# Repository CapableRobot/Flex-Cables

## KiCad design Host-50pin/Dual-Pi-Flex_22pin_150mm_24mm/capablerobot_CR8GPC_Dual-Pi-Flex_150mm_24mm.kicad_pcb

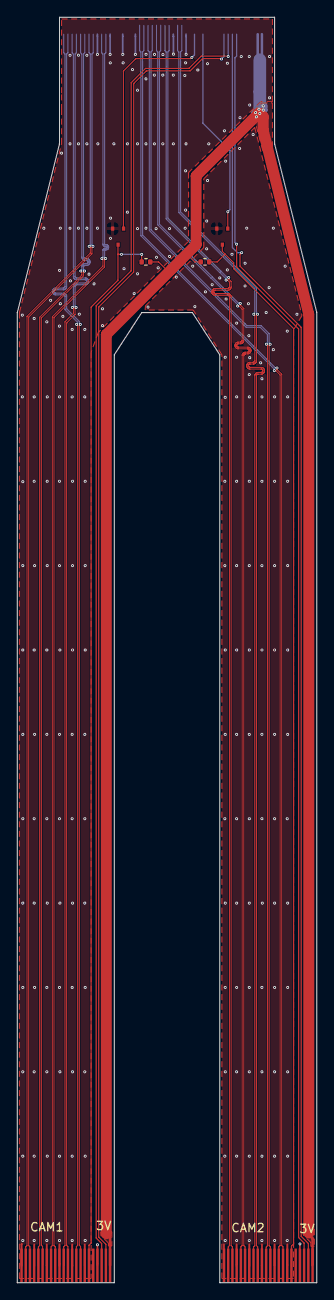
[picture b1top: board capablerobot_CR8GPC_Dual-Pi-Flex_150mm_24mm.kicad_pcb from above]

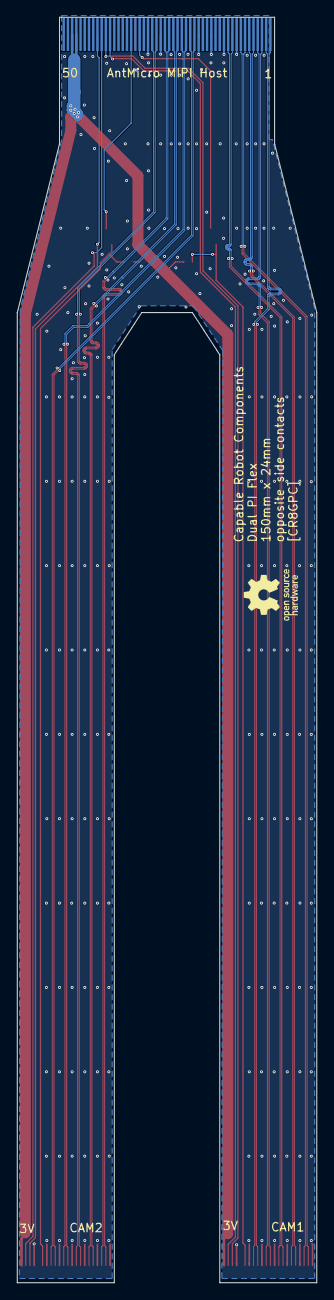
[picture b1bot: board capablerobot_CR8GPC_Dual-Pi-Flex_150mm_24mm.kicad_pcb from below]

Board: 2 copper layers, 35.5 x 150.0 mm, 8 parts (2 on the bottom side), 30 nets.

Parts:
AntMicro MIPI Host: WE_687650100002_FLEX
CAM1, CAM2: WE_687622100002_FLEX
N1: oshw_logo; oshw-logo
Q1, Q2: BSS138APW; SC70-3
R1, R2: R; R_0402_1005Metric

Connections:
/F1_3.3V: AntMicro MIPI Host.47, AntMicro MIPI Host.48, CAM1.22, CAM2.22, R1.2, R2.2
/F1_C1_CSI0_CLK_N: AntMicro MIPI Host.10, CAM1.8
/F1_C1_CSI0_CLK_P: AntMicro MIPI Host.11, CAM1.9
/F1_C1_CSI0_D0_N: AntMicro MIPI Host.7, CAM1.2
/F1_C1_CSI0_D0_P: AntMicro MIPI Host.8, CAM1.3
/F1_C1_CSI0_D1_N: AntMicro MIPI Host.5, CAM1.5
/F1_C1_CSI0_D1_P: AntMicro MIPI Host.6, CAM1.6
/F1_C1_CSI1_D0_N: AntMicro MIPI Host.3, CAM1.11
/F1_C1_CSI1_D0_P: AntMicro MIPI Host.4, CAM1.12
/F1_C1_CSI1_D1_N: AntMicro MIPI Host.1, CAM1.14
/F1_C1_CSI1_D1_P: AntMicro MIPI Host.2, CAM1.15
/F1_C1_SCL: AntMicro MIPI Host.40, CAM1.20
/F1_C1_SDA: AntMicro MIPI Host.39, CAM1.21
/F1_C1_VSYNC: AntMicro MIPI Host.32, Q1.1
/F1_C1_VSYNCHV: CAM1.17, Q1.3, R1.1
/F1_C2_CSI0_CLK_N: AntMicro MIPI Host.28, CAM2.8
/F1_C2_CSI0_CLK_P: AntMicro MIPI Host.29, CAM2.9
/F1_C2_CSI0_D0_N: AntMicro MIPI Host.25, CAM2.2
/F1_C2_CSI0_D0_P: AntMicro MIPI Host.26, CAM2.3
/F1_C2_CSI0_D1_N: AntMicro MIPI Host.23, CAM2.5
/F1_C2_CSI0_D1_P: AntMicro MIPI Host.24, CAM2.6
/F1_C2_CSI1_D0_N: AntMicro MIPI Host.21, CAM2.11
/F1_C2_CSI1_D0_P: AntMicro MIPI Host.22, CAM2.12
/F1_C2_CSI1_D1_N: AntMicro MIPI Host.19, CAM2.14
/F1_C2_CSI1_D1_P: AntMicro MIPI Host.20, CAM2.15
/F1_C2_SCL: AntMicro MIPI Host.42, CAM2.20
/F1_C2_SDA: AntMicro MIPI Host.41, CAM2.21
/F1_C2_VSYNC: AntMicro MIPI Host.34, Q2.1
/F1_C2_VSYNCHV: CAM2.17, Q2.3, R2.1
/F1_GND: AntMicro MIPI Host.9, AntMicro MIPI Host.12, AntMicro MIPI Host.15, AntMicro MIPI Host.18, AntMicro MIPI Host.27, AntMicro MIPI Host.30, CAM1.1, CAM1.4, CAM1.7, CAM1.10, CAM1.13, CAM1.16, CAM1.19, CAM2.1, CAM2.4, CAM2.7, CAM2.10, CAM2.13, CAM2.16, CAM2.19, Q1.2, Q2.2

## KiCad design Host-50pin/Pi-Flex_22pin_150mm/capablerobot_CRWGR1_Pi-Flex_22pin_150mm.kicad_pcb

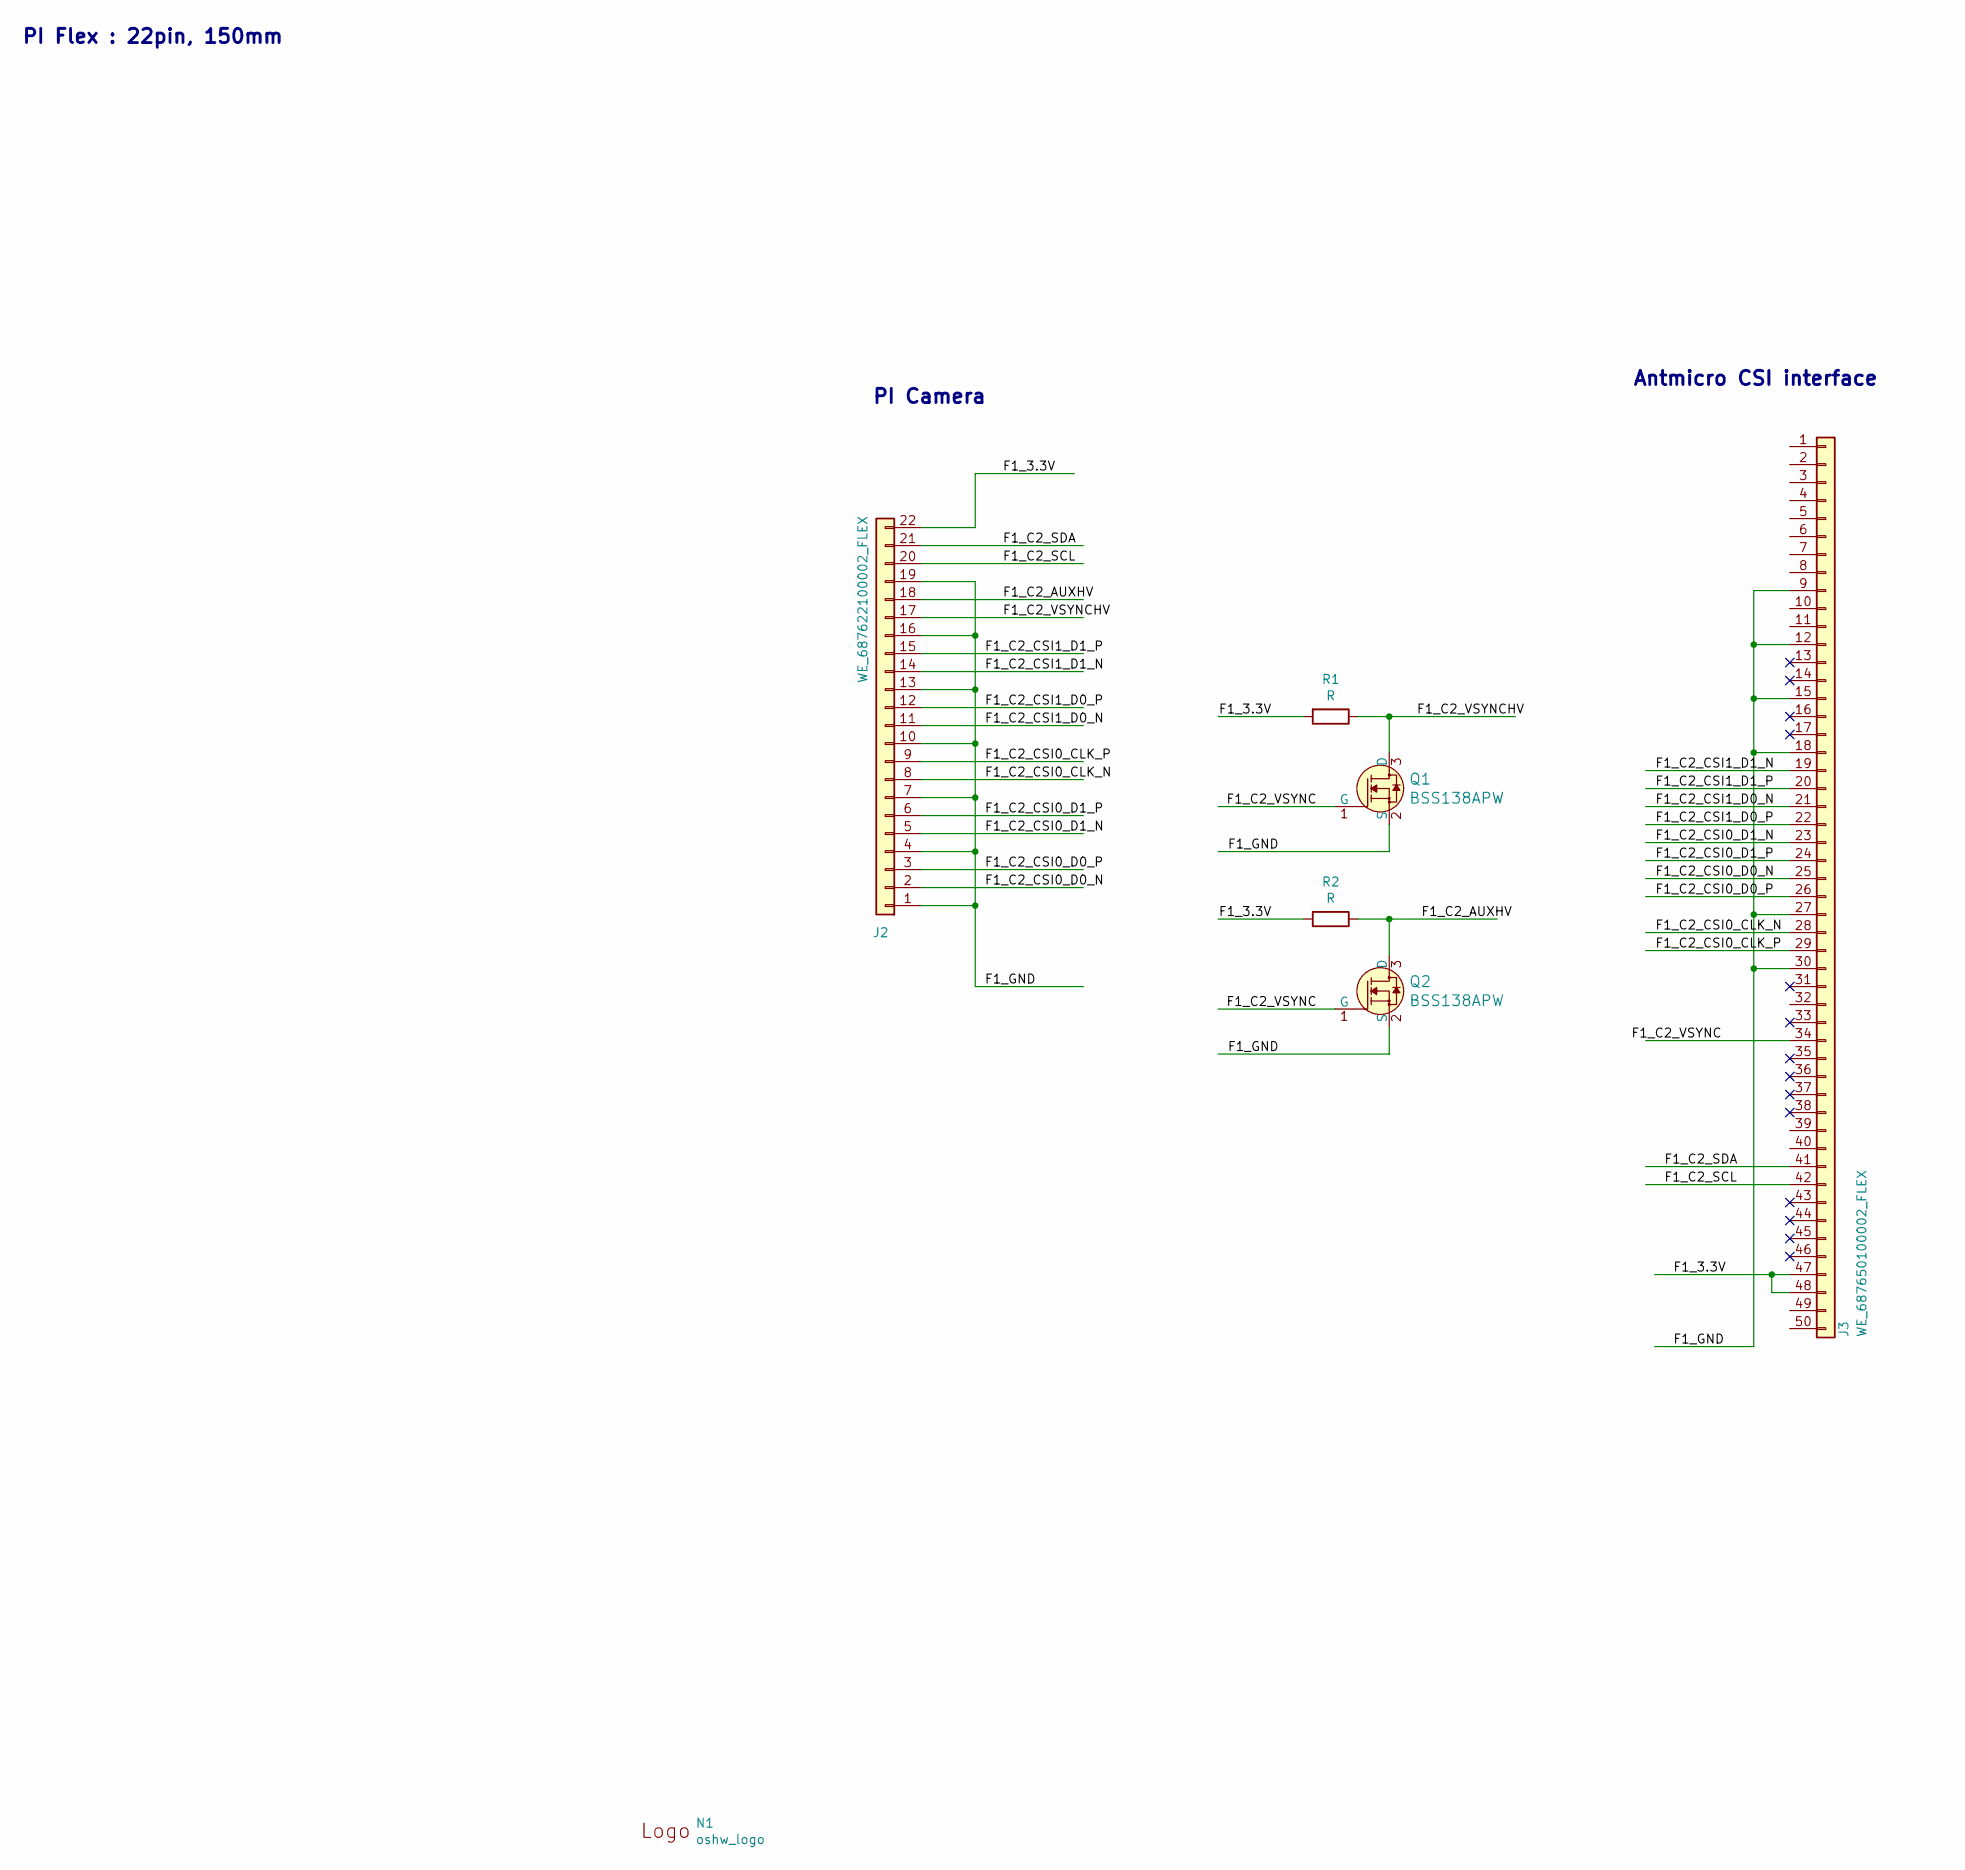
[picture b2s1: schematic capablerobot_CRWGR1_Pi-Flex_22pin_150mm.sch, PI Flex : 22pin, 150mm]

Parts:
J2: WE_687622100002_FLEX; MPN 687622100002
J3: WE_687650100002_FLEX; MPN 687650100002
N1: oshw_logo; oshw-logo
Q1, Q2: BSS138APW; SC70-3; MPN BSS138PW
R1, R2: R; R_0402_1005Metric

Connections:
/F1_3.3V: J2.22, J3.47, J3.48, R1.2, R2.2
/F1_C2_AUXHV: J2.18, Q2.3 (D), R2.1
/F1_C2_CSI0_CLK_N: J2.8, J3.28
/F1_C2_CSI0_CLK_P: J2.9, J3.29
/F1_C2_CSI0_D0_N: J2.2, J3.25
/F1_C2_CSI0_D0_P: J2.3, J3.26
/F1_C2_CSI0_D1_N: J2.5, J3.23
/F1_C2_CSI0_D1_P: J2.6, J3.24
/F1_C2_CSI1_D0_N: J2.11, J3.21
/F1_C2_CSI1_D0_P: J2.12, J3.22
/F1_C2_CSI1_D1_N: J2.14, J3.19
/F1_C2_CSI1_D1_P: J2.15, J3.20
/F1_C2_SCL: J2.20, J3.42
/F1_C2_SDA: J2.21, J3.41
/F1_C2_VSYNC: J3.34, Q1.1 (G), Q2.1 (G)
/F1_C2_VSYNCHV: J2.17, Q1.3 (D), R1.1
/F1_GND: J2.1, J2.4, J2.7, J2.10, J2.13, J2.16, J2.19, J3.9, J3.12, J3.15, J3.18, J3.27, J3.30, Q1.2 (S), Q2.2 (S)

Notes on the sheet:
PI Camera
Antmicro CSI interface
PI Flex : 22pin, 150mm

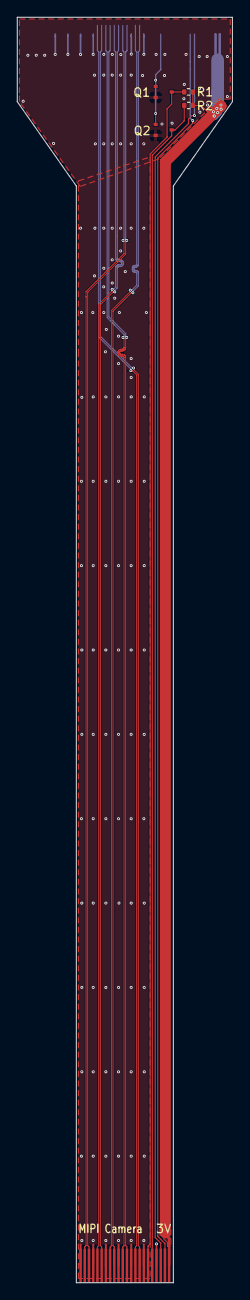
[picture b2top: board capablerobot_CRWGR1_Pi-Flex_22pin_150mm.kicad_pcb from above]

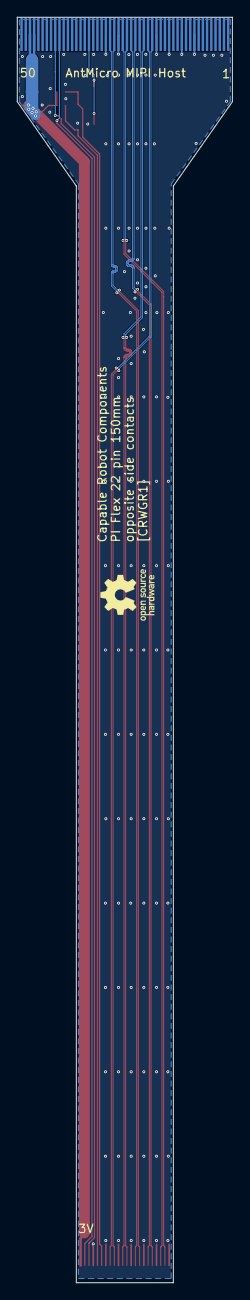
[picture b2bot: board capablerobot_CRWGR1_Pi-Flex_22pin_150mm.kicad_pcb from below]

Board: 2 copper layers, 25.5 x 150.0 mm, 7 parts (2 on the bottom side), 17 nets.

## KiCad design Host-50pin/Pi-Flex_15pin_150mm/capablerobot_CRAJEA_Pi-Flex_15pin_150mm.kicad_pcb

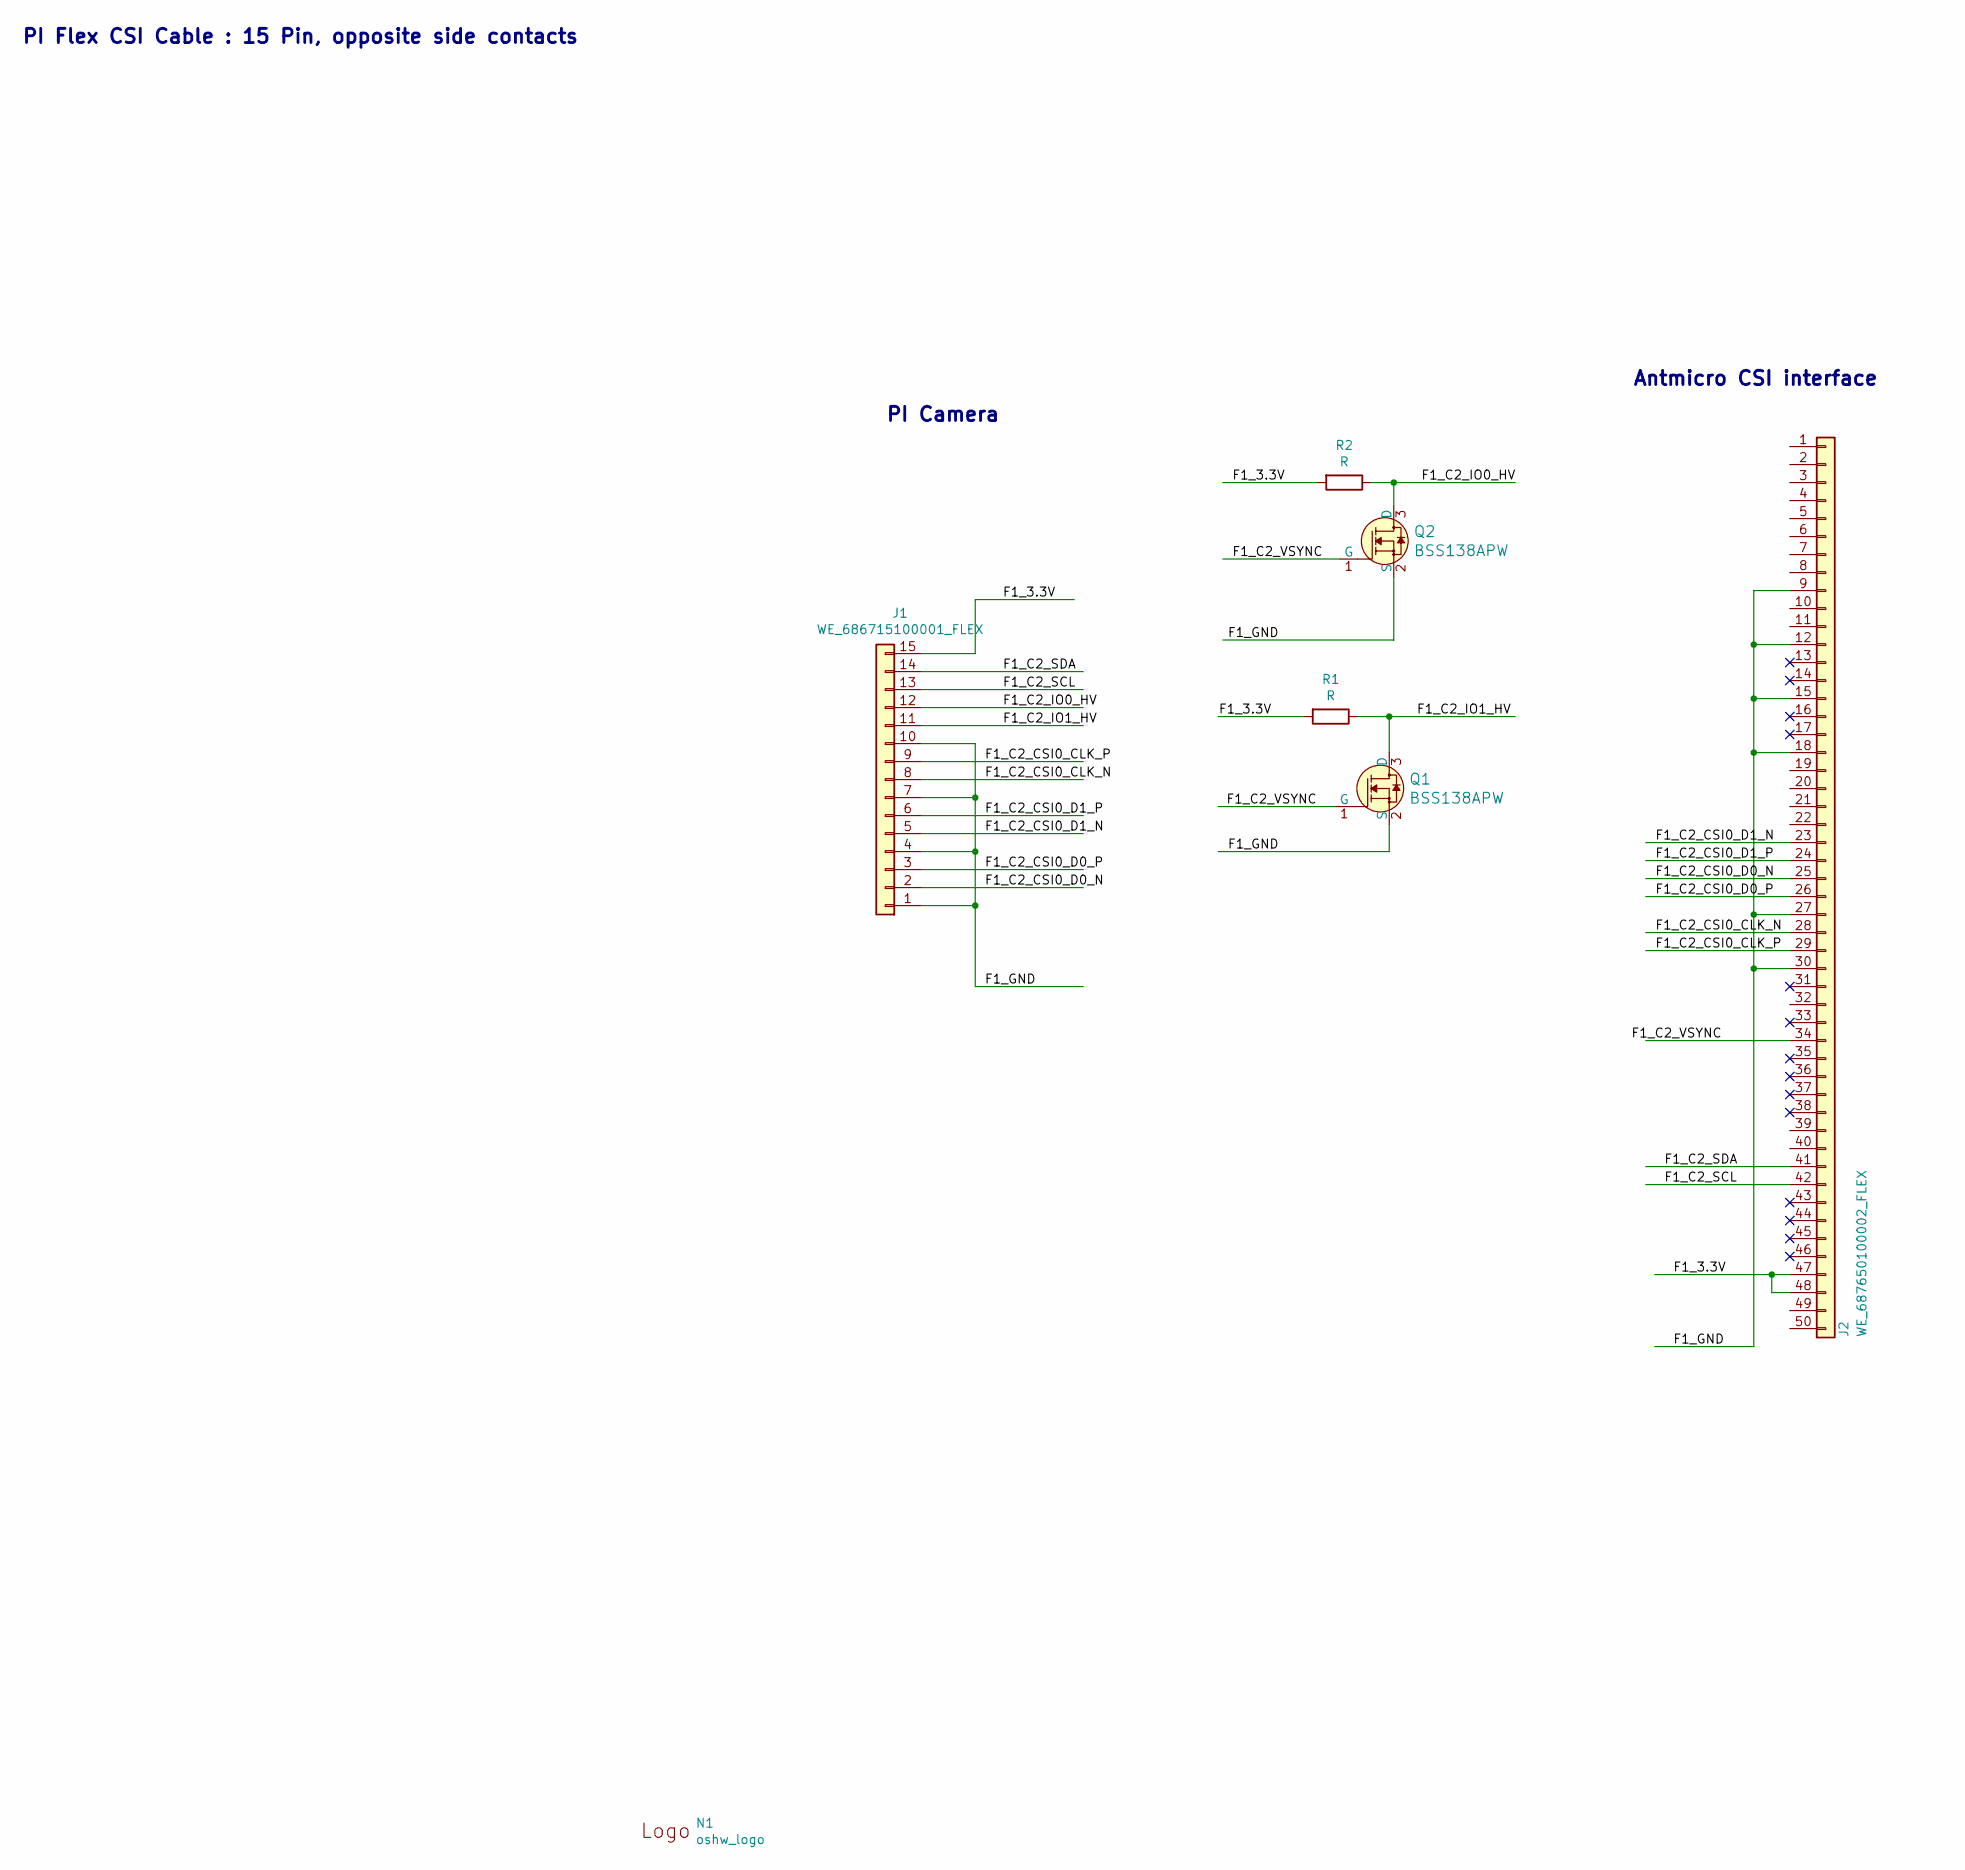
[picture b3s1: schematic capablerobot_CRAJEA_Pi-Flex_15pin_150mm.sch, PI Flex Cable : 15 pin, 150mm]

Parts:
J1: WE_686715100001_FLEX; WE_ 686715100001_FLEX; MPN 686715100001
J2: WE_687650100002_FLEX; MPN 687650100002
N1: oshw_logo; oshw-logo
Q1, Q2: BSS138APW; SC70-3; MPN BSS138PW
R1, R2: R; R_0402_1005Metric

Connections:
/F1_3.3V: J1.15, J2.47, J2.48, R1.2, R2.2
/F1_C2_CSI0_CLK_N: J1.8, J2.28
/F1_C2_CSI0_CLK_P: J1.9, J2.29
/F1_C2_CSI0_D0_N: J1.2, J2.25
/F1_C2_CSI0_D0_P: J1.3, J2.26
/F1_C2_CSI0_D1_N: J1.5, J2.23
/F1_C2_CSI0_D1_P: J1.6, J2.24
/F1_C2_IO0_HV: J1.12, Q2.3 (D), R2.1
/F1_C2_IO1_HV: J1.11, Q1.3 (D), R1.1
/F1_C2_SCL: J1.13, J2.42
/F1_C2_SDA: J1.14, J2.41
/F1_C2_VSYNC: J2.34, Q1.1 (G), Q2.1 (G)
/F1_GND: J1.1, J1.4, J1.7, J1.10, J2.9, J2.12, J2.15, J2.18, J2.27, J2.30, Q1.2 (S), Q2.2 (S)

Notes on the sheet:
PI Camera
Antmicro CSI interface
PI Flex CSI Cable : 15 Pin, opposite side contacts

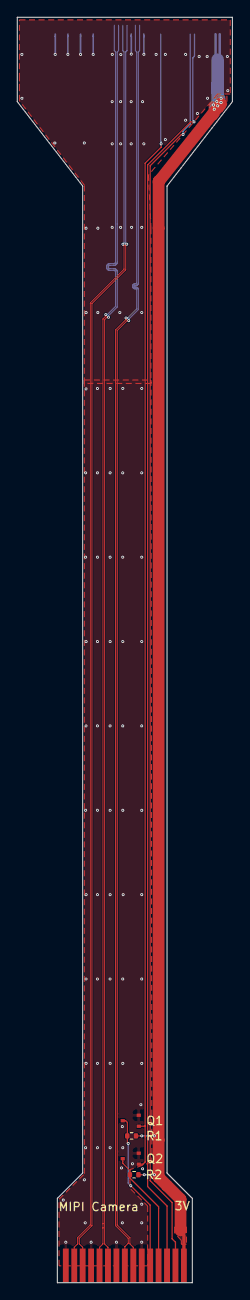
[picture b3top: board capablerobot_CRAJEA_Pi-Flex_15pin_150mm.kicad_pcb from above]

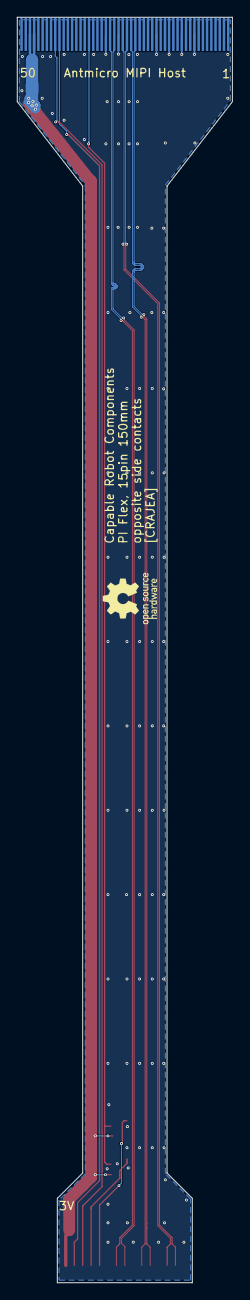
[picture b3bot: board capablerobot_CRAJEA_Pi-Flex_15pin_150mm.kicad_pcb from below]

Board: 2 copper layers, 25.5 x 150.0 mm, 7 parts (2 on the bottom side), 13 nets.

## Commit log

2021-01-04 Commiting CSI cable and library additions
2021-01-04 Sync nets to double up I2C pins and add RST / IO connection
2021-01-04 Rename file and folders
2021-01-04 Adding cable to 22 pin 0.5 pitch host
2021-01-04 Fix title block
2021-01-04 Add schmatic PDFs
2021-04-28 Adding 150mm PI flex cable
2021-06-07 Change silk text
2021-06-07 Add PNG
2021-06-07 Add 22pin dual PI flex cable
2021-06-07 Add 22pin PI flex cable
2021-06-07 Add PDF of schematic
2021-06-07 Label components
2021-06-07 Update PNG
2021-06-07 Update silk text
2021-06-07 Change 22 pin to 4 lane interface and change 15 pin and 22 pin to alternate MIPI interface
2021-06-22 Update title blocks and regenrate PDFs
